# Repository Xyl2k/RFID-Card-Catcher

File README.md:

# NFC/RFID Card Catcher v0.1
* Recording NFC/RFID cards for fun and hacking
* Original idea from a french television program "On n'est plus des pigeons"

# Requirements
* Arduino Mega 2560
* SD Card Reader
* Adafruit PN532

# Does it work ?
* Half, for an unknown reason SD reader can't work while PN532 is working, i suppose the problem come from the SPI.
However i've decided to release my code till i (or someone) fix it or change the wiring of the PN532 to I²C bus.

# Warning
* Regarding to the Eagle board layout, i know there is no reason yet to make it but anyway i've designed it to use a specific SD Card reader who can be bought on DealeXtreme, detail can be found on the header of Catcher.ino

# License

WTFPL (see license.txt)

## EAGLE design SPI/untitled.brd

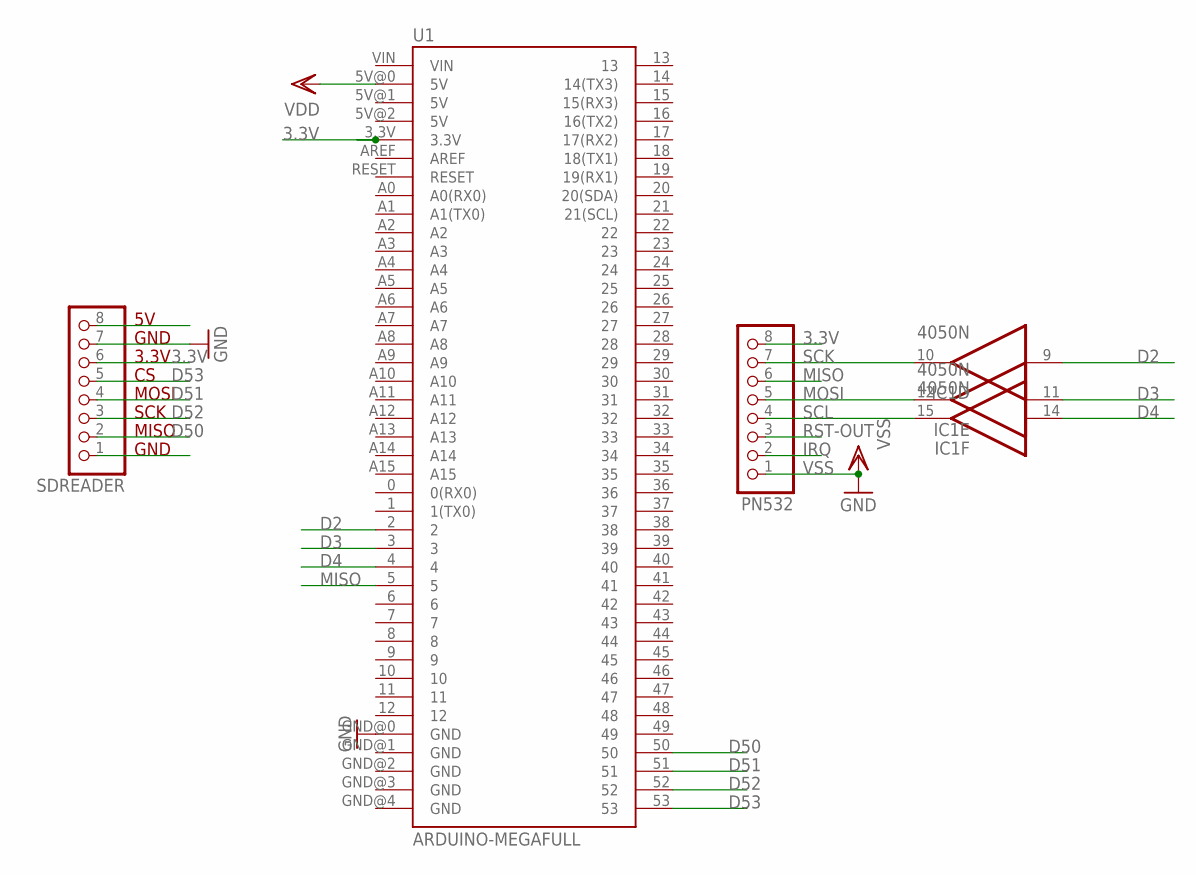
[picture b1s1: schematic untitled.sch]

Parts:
IC1: 4050N; DIL16
PN532: PINHD-1X8BIG; 1X08-BIG
SDREADER: PINHD-1X8BIG; 1X08-BIG
U1: ARDUINO-MEGAFULL; ARDUINO_MEGA

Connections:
3.3V: PN532.8, SDREADER.6, U1.3.3V
D2: IC1.9 (I), U1.2
D3: IC1.11 (I), U1.3
D4: IC1.14 (I), U1.4
D50: SDREADER.2, U1.50
D51: SDREADER.4, U1.51
D52: SDREADER.3, U1.52
D53: SDREADER.5, U1.53
GND: SDREADER.7, U1.GND@0 (GND)
IRQ: PN532.2
MISO: PN532.6, U1.5
MOSI: IC1.12 (O), PN532.5
RST-OUT: PN532.3
SCK: IC1.10 (O), PN532.7
SCL: IC1.15 (O), PN532.4
VDD: IC1.1 (VDD), U1.5V@0 (5V)
VSS: IC1.8 (VSS), PN532.1

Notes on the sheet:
GND
3.3V
MOSI
SCK
MISO

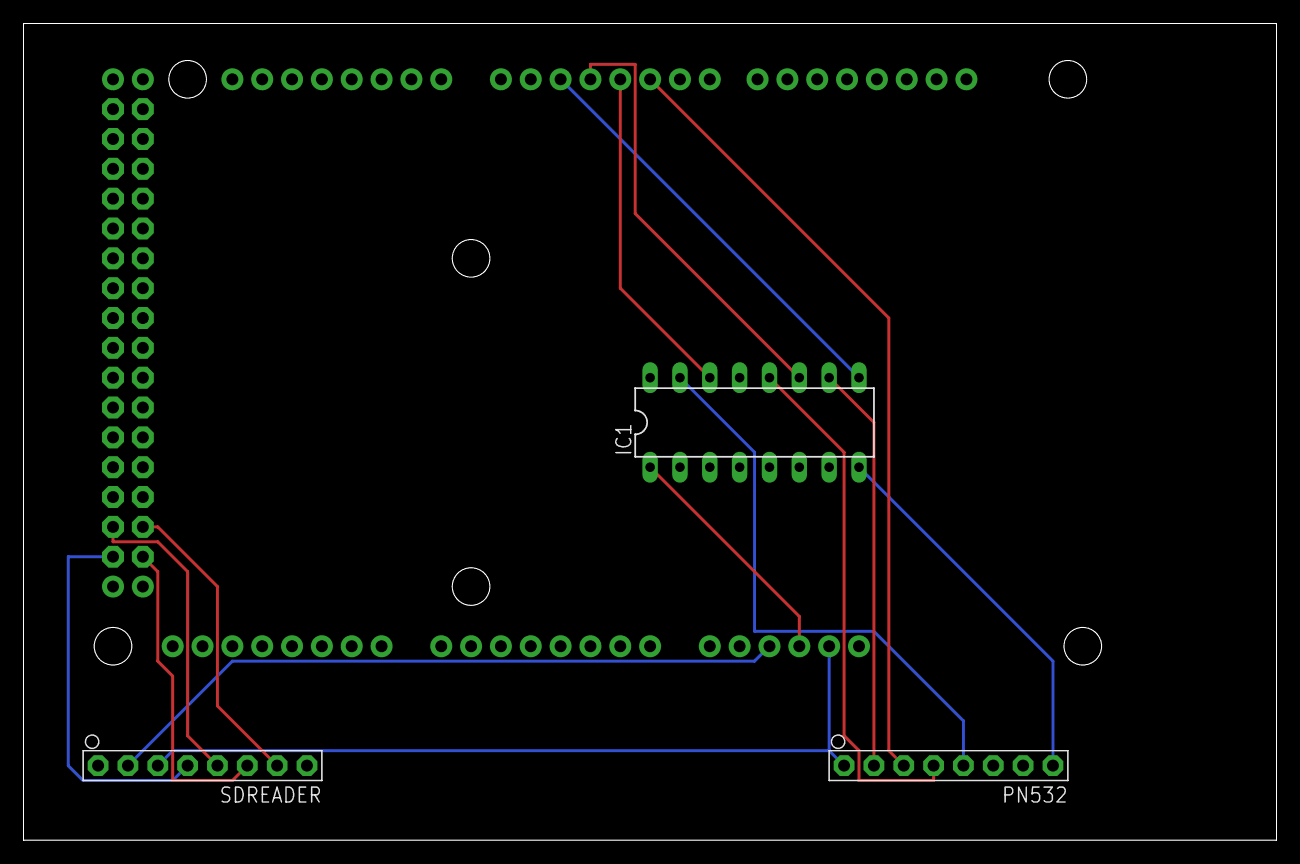
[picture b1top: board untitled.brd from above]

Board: 2 copper layers, 106.7 x 69.5 mm, 4 parts (1 on the bottom side), 15 nets.

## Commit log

2015-05-15 :tada: Added .gitattributes & .gitignore files
2015-05-15 0.1
    0.1

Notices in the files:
parts and their libraries:
ardiuno: Licensing: Creative Commons ShareAlike 4.0 International - https://creativecommons.org/licenses/by-sa/4.0
